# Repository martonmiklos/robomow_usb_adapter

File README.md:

## FT231x based converter to RJ11 connector

Size: 42.44 x 17.78 mm

Drawn in EAGLE 9.x

Warning pozor!! The TX/RX is swapped in the board in the repo, however I stopped using EAGLE and it is not likely, that I am going to fix it.
At some point I might recreate the design in Kicad.

The board has two variants:

### Robomow interface for RM-5xx series 

Normal UART 5V operation for used with Robomow RM toolkit.

You need to invert the both TX and RX lines with the [FT_Prog](https://ftdichip.com/utilities/#ft_prog).

Pinout:

### RS-485 adapter for Sorensen/Ametek DLM series power supplies

For communicating Sorensen DLM series power supplies via RS-485

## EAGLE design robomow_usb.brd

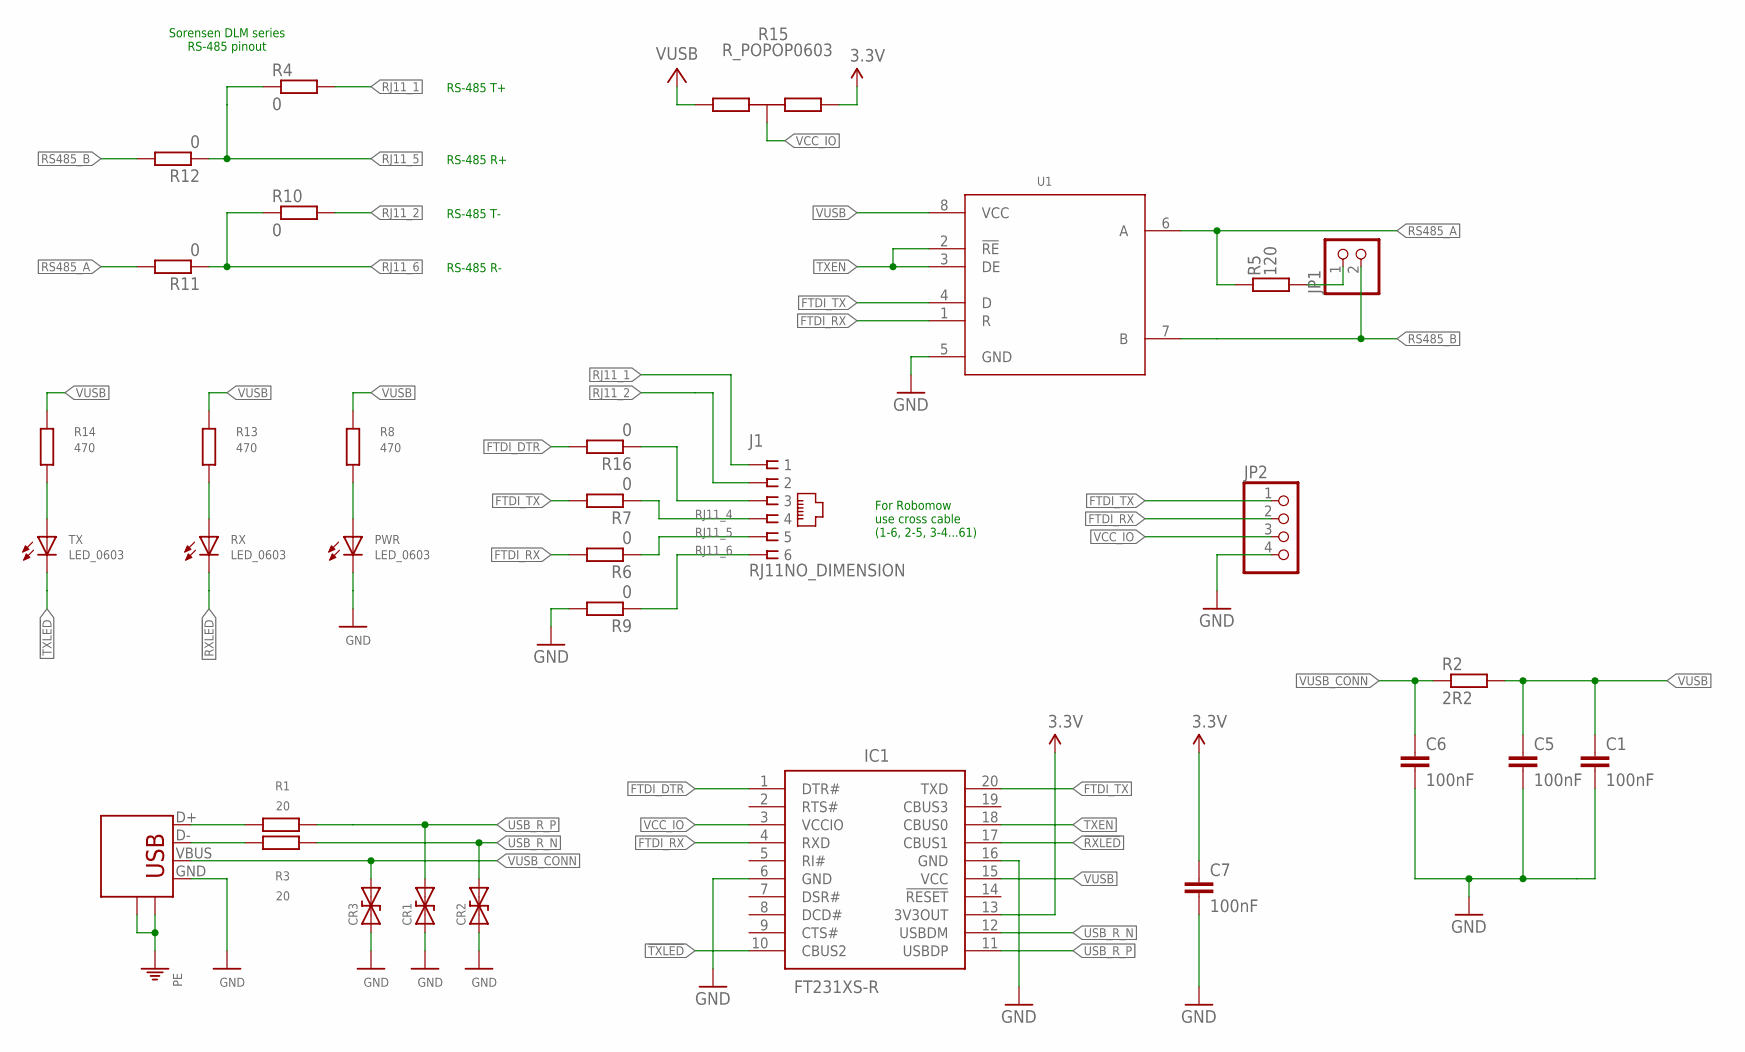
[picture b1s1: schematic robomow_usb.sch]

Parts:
C1, C5, C6, C7: 100nF; C0603
CR1, CR2, CR3: 0603ESDA2-TR2; 0603
IC1: FT231XS-R; SOP64P599X175-20N
J1: RJ11NO_DIMENSION; RJ11-NO_SHIELD_NO_DIMENSION
JP1: PINHD-1X2; 1X02
JP2: PINHD-1X4; 1X04
JUSB: USBPTH; USB-B-PTH
PWR: LED_0603; LED-603
R1, R3: 20; R0603
R2: 2R2; R0603
R4, R6, R7, R9, R10, R11, R12, R16: 0; R0603
R5: 120; R0603
R8, R13, R14: 470; R0603
R15: R_POPOP0603; 0603_POPOP
RX: LED_0603; LED-603
TX: LED_0603; LED-603
U1: SN65HVD1176; D0008A_N

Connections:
3.3V: C7.1, IC1.13 (3V3OUT), R15.A
!RXLED: IC1.17 (CBUS1), RX.C
!TXLED: IC1.10 (CBUS2), TX.C
FTDI_DTR: IC1.1 (DTR#), R16.2
FTDI_RX: IC1.4 (RXD), JP2.2, R6.2, U1.1 (R)
FTDI_TX: IC1.20 (TXD), JP2.1, R7.2, U1.4 (D)
GND: C1.2, C5.2, C6.2, C7.2, CR1.1, CR2.1, CR3.1, IC1.6 (GND), IC1.16 (GND), JP2.4, JUSB.GND, PWR.C, R9.2, U1.5 (GND)
unnamed: J1.3, R16.1
PE: JUSB.P$1 (SH1), JUSB.P$2 (SH2)
RJ11_1: J1.1, R4.2
RJ11_2: J1.2, R10.2
RJ11_4: J1.4, R7.1
RJ11_5: J1.5, R4.1, R6.1, R12.1
RJ11_6: J1.6, R9.1, R10.1, R11.1
RS485_A: R5.1, R11.2, U1.6 (A)
RS485_B: JP1.2, R12.2, U1.7 (B)
RS485_TERM_ENABLE: JP1.1, R5.2
TXEN: IC1.18 (CBUS0), U1.2 (!RE), U1.3 (DE)
USB_N: JUSB.D-, R3.2
USB_P: JUSB.D+, R1.2
USB_R_N: CR2.2, IC1.12 (USBDM), R3.1
USB_R_P: CR1.2, IC1.11 (USBDP), R1.1
VCC_IO: IC1.3 (VCCIO), JP2.3, R15.COM
VIN_LED_R1: PWR.A, R8.2
VIN_LED_R2: R13.2, RX.A
VIN_LED_R3: R14.2, TX.A
VUSB: C1.1, C5.1, IC1.15 (VCC), R2.2, R8.1, R13.1, R14.1, R15.A1 (B), U1.8 (VCC)
VUSB_CONN: C6.1, CR3.2, JUSB.VBUS, R2.1

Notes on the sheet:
Sorensen DLM series RS-485 pinout
RS-485 T+
RS-485 R+
RS-485 T-
RS-485 R-
For Robomow use cross cable (1-6, 2-5, 3-4...61)

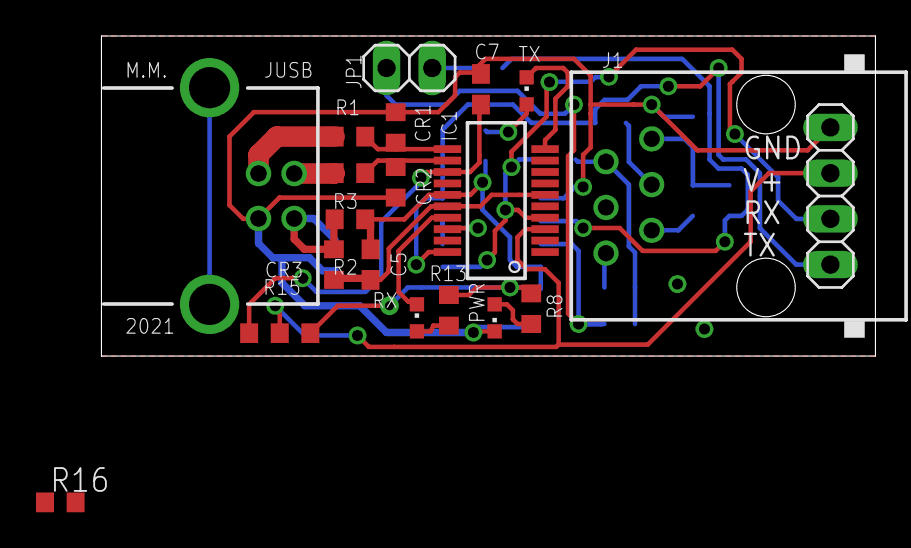
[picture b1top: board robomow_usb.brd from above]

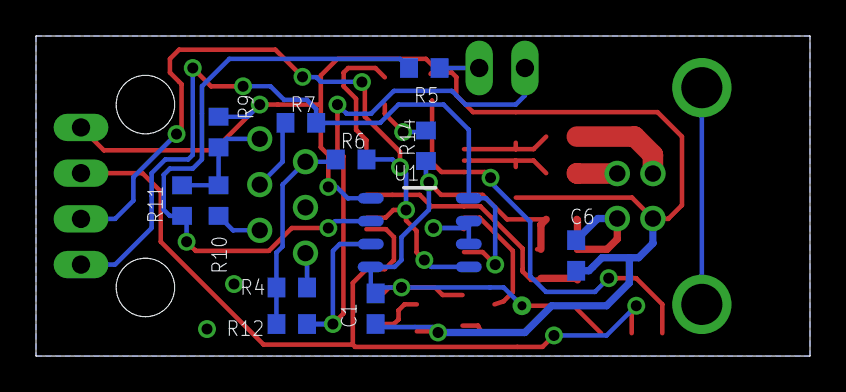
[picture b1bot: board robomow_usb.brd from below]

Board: 2 copper layers, 43.0 x 17.8 mm, 32 parts (12 on the bottom side), 28 nets.

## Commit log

2020-12-17 Polish routing
2020-12-17 Images regenerated
2020-12-17 Save
2020-12-19 Added TX RX LEDs
2021-05-05 Full pass on DRC (removed stubs)
2021-06-20 Fixup input filtering
2022-09-30 Pimp readme
2022-10-02 Connect DTR (used for boot trigger) for the Robomow mode Thanks Ryan!
2023-05-09 Update README.md
    Add note about the TX/RX inversion
2024-04-07 Update README, fix pinout in the image
